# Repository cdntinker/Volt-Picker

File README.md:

This is a little USB-PD board that'll give you the selected output voltage if plugged into a PD capable source that supports the chosen voltage.

# Theory:
One of the main design criteria is that it does NOT require an MCU to manage it.

Voltage & Current are chosen by soldering a jumper for each.  (The basic circuit can easily be embeded into a board with just a single resistor for each...)

# Rant/Snark:
* Volt-Picker 1.tar.gz:
  * My original design idea
  * Based on the CH224 from Nanjing Qinheng Microelectronics Co., Ltd. (WCH)
  * chip seems to have been disontinued...
* Volt-Picker 2.tar.gz
  * New design based on the AP33771 from Diodes Incorporated
  * Apparently, this has been replaced by the AP33771C
  * But nobody has stock yet...
* This is now rev 3.0.0
  * Based on the AP33771C
  * Will it be the penultimate verion?
  * Only time will tell if there's a need for a rev 4...

# Notes:
FreeCAD's STEP export seems to have some sort of bug that occasionally causes random boolean cuts in CSG objects to act like boolean unions.  This is very weird and annoying.

My current solution (seems to work rather well...) is to go back into the project and add 0.001mm to a positional offset of the item that's being borked.

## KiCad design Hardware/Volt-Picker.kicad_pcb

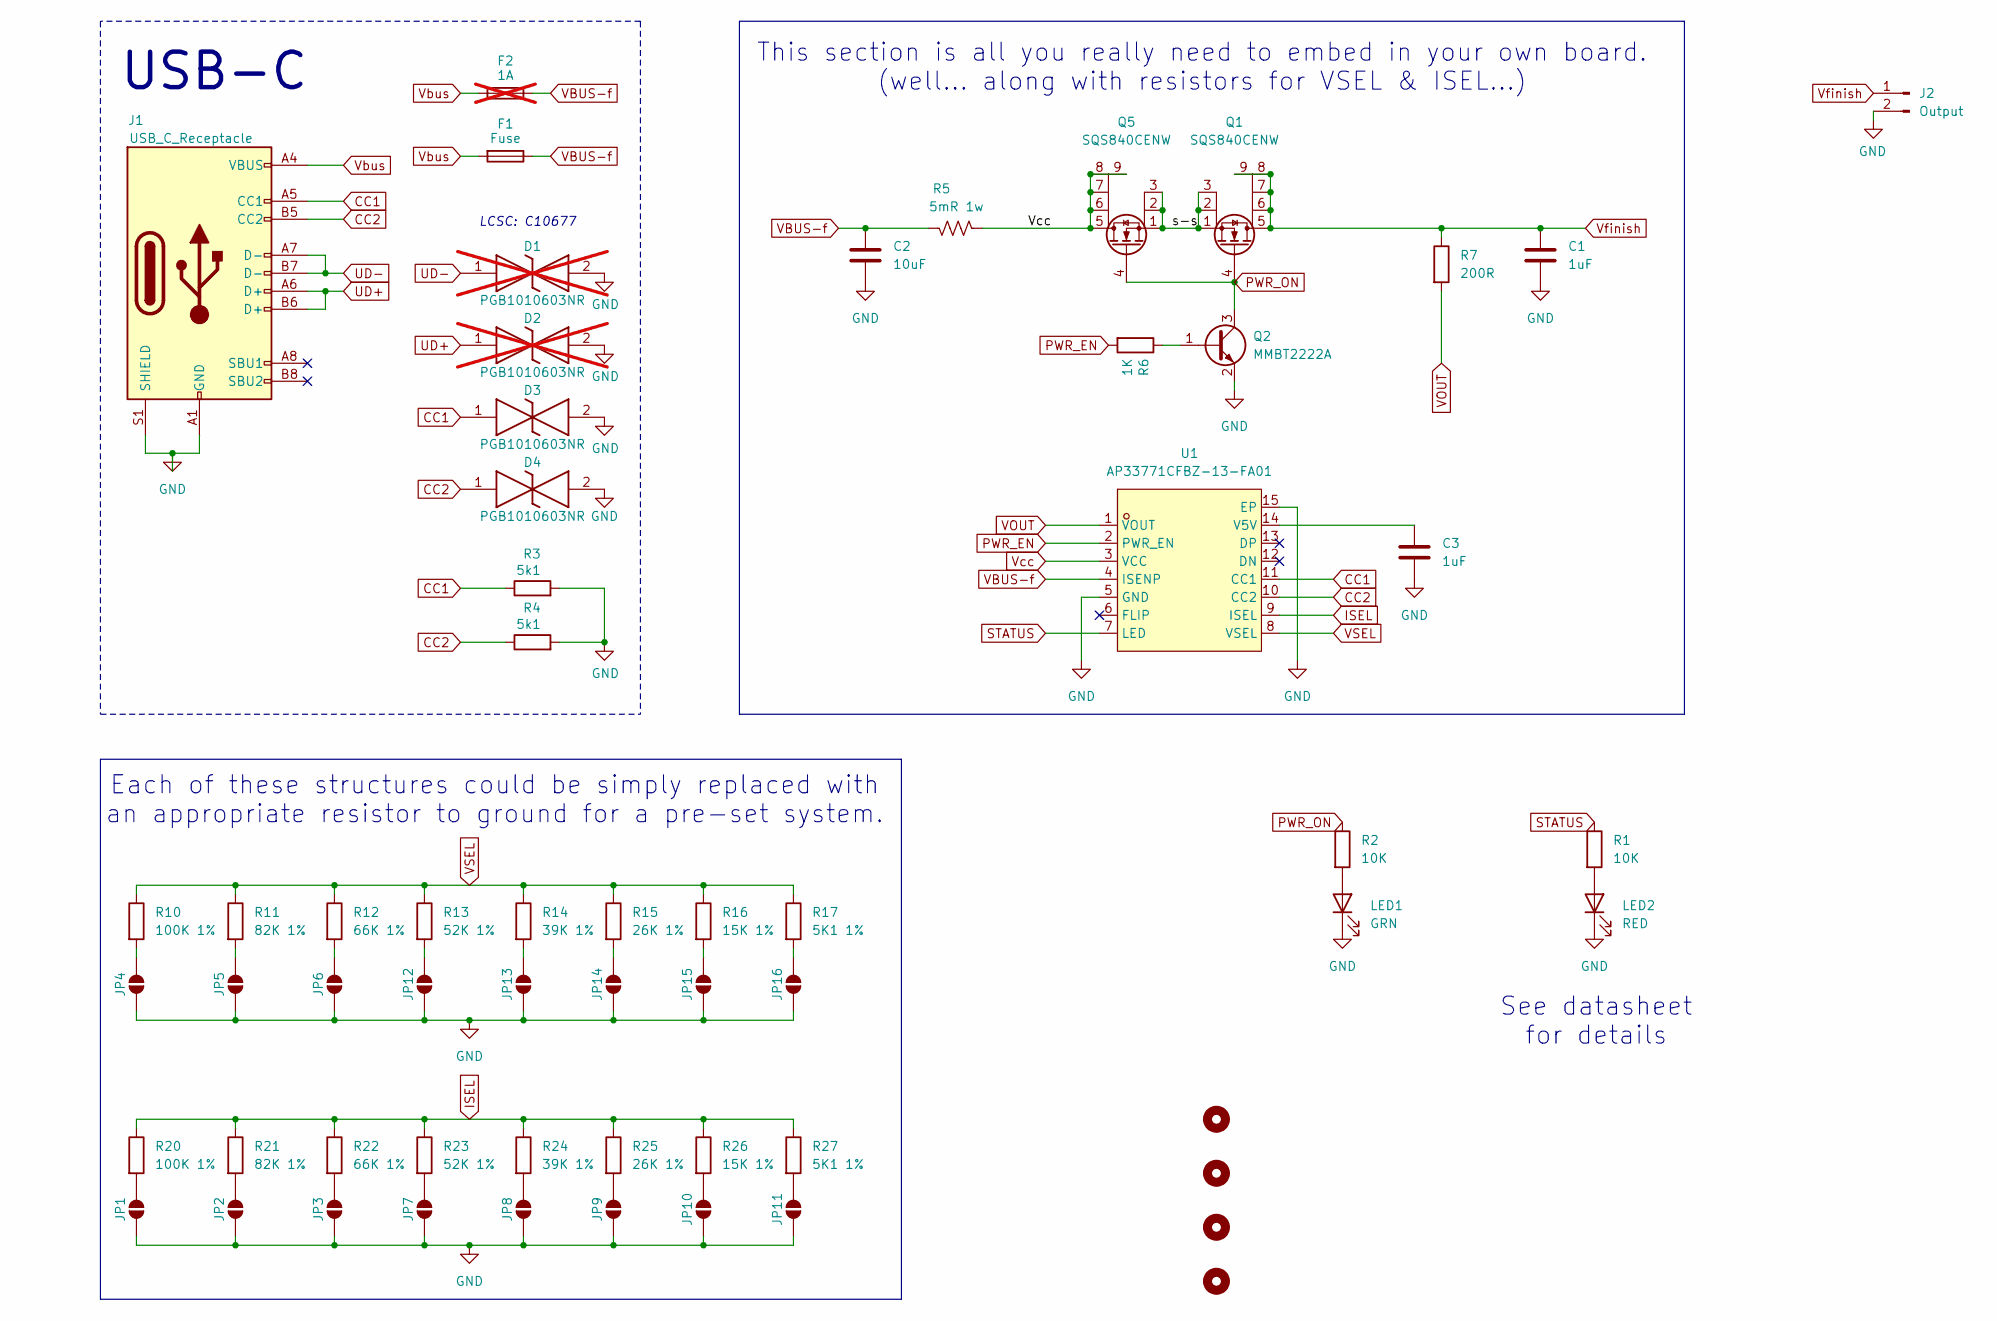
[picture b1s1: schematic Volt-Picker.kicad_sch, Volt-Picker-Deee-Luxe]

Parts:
C1: 1uF; C_0805_2012Metric; LCSC C28323
C2: 10uF; C_0805_2012Metric
C3: 1uF; C_0603_1608Metric; LCSC C28323
D1, D2: PGB1010603NR; PGB1010603NRHF; Manufacturer_Part_Number PGB1010603NR; Mouser Part Number 576-PGB1010603NR; not fitted
D3, D4: PGB1010603NR; PGB1010603NRHF; Manufacturer_Part_Number PGB1010603NR; Mouser Part Number 576-PGB1010603NR
F1: Fuse; Fuseholder_Littelfuse_Nano2_154x; LCSC Part C206922 (maybe)
F2: 1A; Fuse_1206_3216Metric_Pad1.42x1.75mm_HandSolder; LCSC C41367221; not fitted
H1, H2, H3, H4: MountingHole; MountingHole_3.2mm_M3_DIN965
J1: USB_C_Receptacle; USB_C_Receptacle_HRO_TYPE-C-31-M-12; LCSC C2765186
J2: Output; TerminalBlock_DG350-3.5-02P-14-00A(H); LCSC C2760668
JP1, JP2, JP3, JP4, JP5, JP6, JP7, JP8, JP9, JP10, JP11, JP12, JP13, JP14, JP15, JP16: SolderJumper_2_Open; tinySJ-Open (alt)
LED1: GRN; LED_0603_1608Metric; LCSC C2994781
LED2: RED; LED_0603_1608Metric; LCSC C2994781
Q1, Q5: SQS840CENW; POWERPAK-1212-8_L3.1-W3.1-P0.65-LS3.3-BL
Q2: MMBT2222A; SOT-23; LCSC Part C916372
R1, R2: 10K; R_0603_1608Metric
R3, R4: 5k1; R_0603_1608Metric; LCSC C23186
R5: 5mR 1w; R_1206_3216Metric
R6: 1K; R_0603_1608Metric; LCSC Part C22548
R7: 200R; R_0603_1608Metric
R10, R20: 100K 1%; R_0603_1608Metric
R11, R21: 82K 1%; R_0603_1608Metric
R12, R22: 66K 1%; R_0603_1608Metric
R13, R23: 52K 1%; R_0603_1608Metric
R14, R24: 39K 1%; R_0603_1608Metric
R15, R25: 26K 1%; R_0603_1608Metric
R16, R26: 15K 1%; R_0603_1608Metric
R17, R27: 5K1 1%; R_0603_1608Metric
U1: AP33771CFBZ-13-FA01; TDFN-14_L3.0-W3.0-P0.40-TL-EP; MPN AP33771CFBZ-13-FA01; LCSC Part C24735840

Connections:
/s-s: Q1.1 (S), Q1.2 (S), Q1.3 (S), Q5.1 (S), Q5.2 (S), Q5.3 (S)
CC1: D3.1, J1.A5 (CC1), R3.1, U1.11 (CC1)
CC2: D4.1, J1.B5 (CC2), R4.1, U1.10 (CC2)
GND: C1.2, C2.2, C3.2, D1.2, D2.2, D3.2, D4.2, J1.A1 (GND), J1.A12 (GND), J1.B1 (GND), J1.B12 (GND), J1.S1 (SHIELD), J2.2, JP1.1 (A), JP2.1 (A), JP3.1 (A), JP4.1 (A), JP5.1 (A), JP6.1 (A), JP7.1 (A), JP8.1 (A), JP9.1 (A), JP10.1 (A), JP11.1 (A), JP12.1 (A), JP13.1 (A), JP14.1 (A), JP15.1 (A), JP16.1 (A), LED1.1 (K), LED2.1 (K), Q2.2 (E), R3.2, R4.2, U1.5 (GND), U1.15 (EP)
ISEL: R20.1, R21.1, R22.1, R23.1, R24.1, R25.1, R26.1, R27.1, U1.9 (ISEL)
unnamed: JP1.2 (B), R20.2
unnamed: JP2.2 (B), R21.2
unnamed: JP3.2 (B), R22.2
unnamed: JP4.2 (B), R10.2
unnamed: JP5.2 (B), R11.2
unnamed: JP6.2 (B), R12.2
unnamed: JP7.2 (B), R23.2
unnamed: JP8.2 (B), R24.2
unnamed: JP9.2 (B), R25.2
unnamed: JP10.2 (B), R26.2
unnamed: JP11.2 (B), R27.2
unnamed: JP12.2 (B), R13.2
unnamed: JP13.2 (B), R14.2
unnamed: JP14.2 (B), R15.2
unnamed: JP15.2 (B), R16.2
unnamed: JP16.2 (B), R17.2
unnamed: LED1.2 (A), R2.2
unnamed: LED2.2 (A), R1.2
unnamed: Q2.1 (B), R6.1
unnamed: C3.1, U1.14 (V5V)
PWR_EN: R6.2, U1.2 (PWR_EN)
PWR_ON: Q1.4 (G), Q2.3 (C), Q5.4 (G), R2.1
STATUS: R1.1, U1.7 (LED)
UD+: D2.1, J1.A6 (D+), J1.B6 (D+)
UD-: D1.1, J1.A7 (D-), J1.B7 (D-)
VBUS-f: C2.1, F1.1, F2.2, R5.2, U1.4 (ISENP)
VOUT: R7.2, U1.1 (VOUT)
VSEL: R10.1, R11.1, R12.1, R13.1, R14.1, R15.1, R16.1, R17.1, U1.8 (VSEL)
Vbus: F1.2, F2.1, J1.A4 (VBUS), J1.A9 (VBUS), J1.B4 (VBUS), J1.B9 (VBUS)
Vcc: Q5.5 (D), Q5.6 (D), Q5.7 (D), Q5.8 (D), Q5.9 (D), R5.1, U1.3 (VCC)
Vfinish: C1.1, J2.1, Q1.5 (D), Q1.6 (D), Q1.7 (D), Q1.8 (D), Q1.9 (D), R7.1

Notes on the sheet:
USB-C
Each of these structures could be simply replaced with an appropriate resistor to ground for a pre-set system.
LCSC: C10677
See datasheet for details
This section is all you really need to embed in your own board. (well... along with resistors for VSEL & ISEL...)

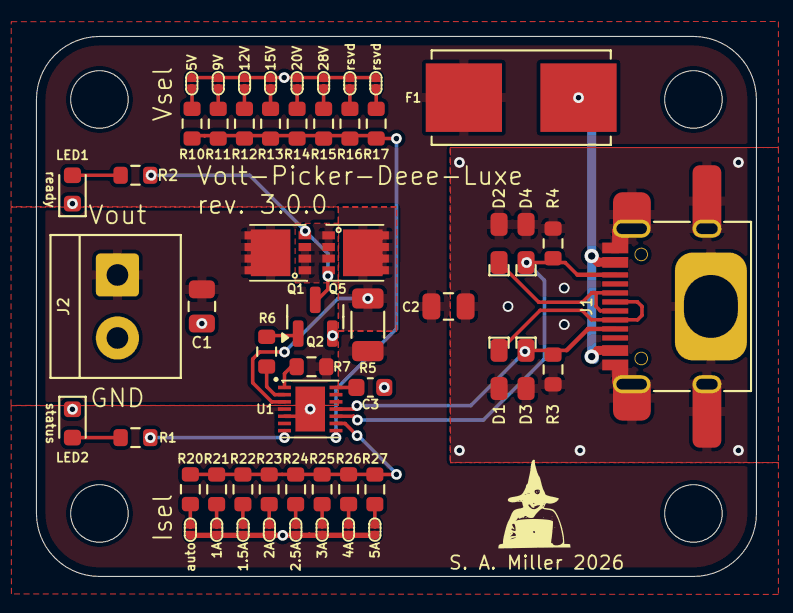
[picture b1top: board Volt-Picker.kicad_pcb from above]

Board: 2 copper layers, 40.0 x 30.0 mm, 59 parts (0 on the bottom side), 36 nets.

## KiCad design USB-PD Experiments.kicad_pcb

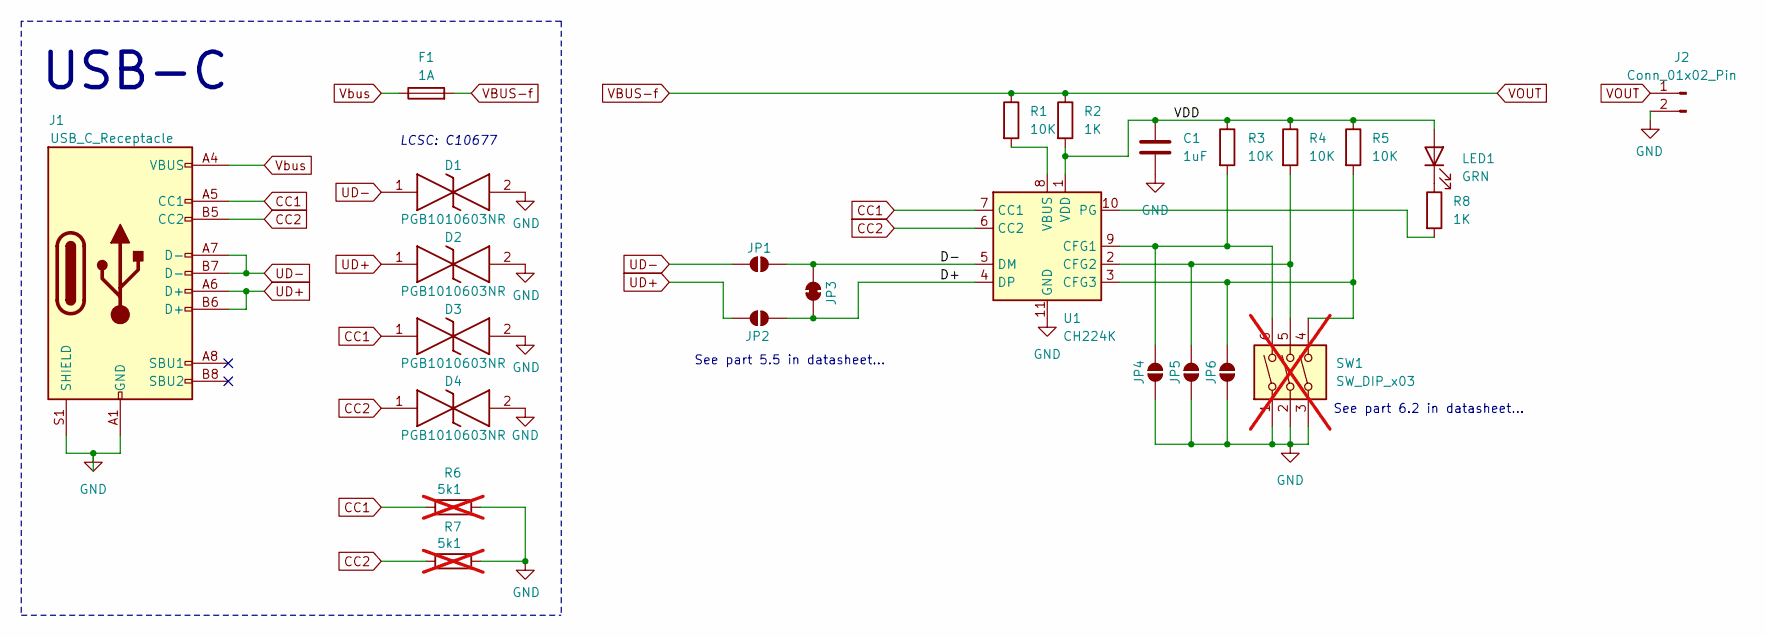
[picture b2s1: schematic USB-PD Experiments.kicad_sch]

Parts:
C1: 1uF; C_0805_2012Metric; LCSC C28323
D1, D2, D3, D4: PGB1010603NR; PGB1010603NRHF; Manufacturer_Part_Number PGB1010603NR; Mouser Part Number 576-PGB1010603NR
F1: 1A; Fuse_1206_3216Metric_Pad1.42x1.75mm_HandSolder; LCSC C41367221
J1: USB_C_Receptacle; USB_C_Receptacle_HRO_TYPE-C-31-M-12; LCSC C2765186
J2: Conn_01x02_Pin; TerminalBlock_DG350-3.5-02P-14-00A(H); LCSC C2760668
JP1, JP2: SolderJumper_2_Open; tinySJ-Open
JP3: SolderJumper_2_Bridged; smallSJ-Bridged
JP4, JP5, JP6: SolderJumper_2_Open; tinySJ-Open (alt)
LED1: GRN; LED_0603_1608Metric; LCSC C2994781
R1, R3, R4, R5: 10K; R_0603_1608Metric; LCSC C25804
R2, R8: 1K; R_0603_1608Metric; LCSC C21190
R6, R7: 5k1; R_0603_1608Metric; LCSC C23186; not fitted
SW1: SW_DIP_x03; SW_DIP_SPSTx03_Slide_KingTek_DSHP03TJ_W5.25mm_P1.27mm_JPin; LCSC C19272175; not fitted
U1: CH224K; SSOP-10-1EP_3.9x4.9mm_P1mm_EP2.1x3.3mm; LCSC C970725

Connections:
/D+: JP2.2 (B), JP3.1 (A), U1.4 (DP)
/D-: JP1.2 (B), JP3.2 (B), U1.5 (DM)
/VDD: C1.1, LED1.2 (A), R2.2, R3.1, R4.1, R5.1, U1.1 (VDD)
CC1: D3.1, J1.A5 (CC1), R6.1, U1.7 (CC1)
CC2: D4.1, J1.B5 (CC2), R7.1, U1.6 (CC2)
GND: C1.2, D1.2, D2.2, D3.2, D4.2, J1.A1 (GND), J1.A12 (GND), J1.B1 (GND), J1.B12 (GND), J1.S1 (SHIELD), J2.2, JP4.1 (A), JP5.1 (A), JP6.1 (A), R6.2, R7.2, SW1.1, SW1.2, SW1.3, U1.11 (GND)
unnamed: JP4.2 (B), R3.2, SW1.6, U1.9 (CFG1)
unnamed: JP5.2 (B), R4.2, SW1.5, U1.2 (CFG2)
unnamed: JP6.2 (B), R5.2, SW1.4, U1.3 (CFG3)
unnamed: LED1.1 (K), R8.1
unnamed: R8.2, U1.10 (PG)
unnamed: R1.2, U1.8 (VBUS)
UD+: D2.1, J1.A6 (D+), J1.B6 (D+), JP2.1 (A)
UD-: D1.1, J1.A7 (D-), J1.B7 (D-), JP1.1 (A)
VBUS-f: F1.2, J2.1, R1.1, R2.1
Vbus: F1.1, J1.A4 (VBUS), J1.A9 (VBUS), J1.B4 (VBUS), J1.B9 (VBUS)

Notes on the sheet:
See part 5.5 in datasheet...
USB-C
See part 6.2 in datasheet...
LCSC: C10677

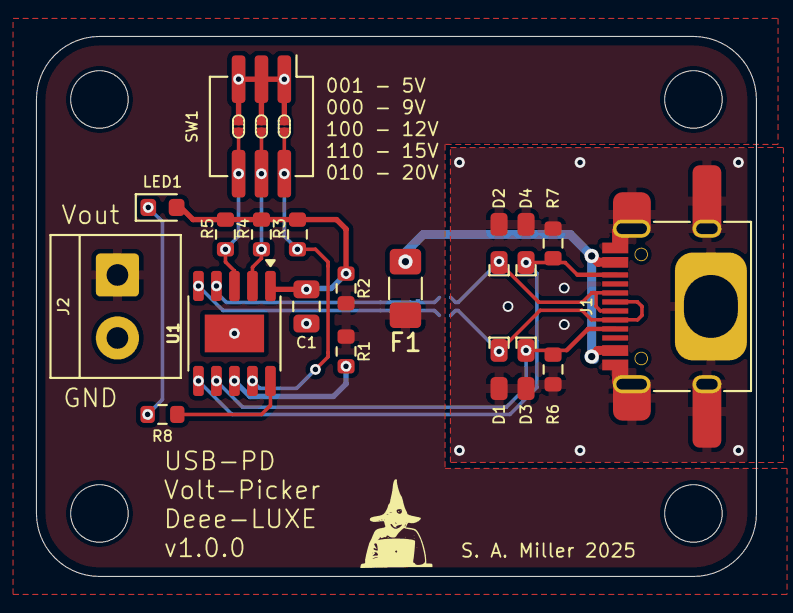
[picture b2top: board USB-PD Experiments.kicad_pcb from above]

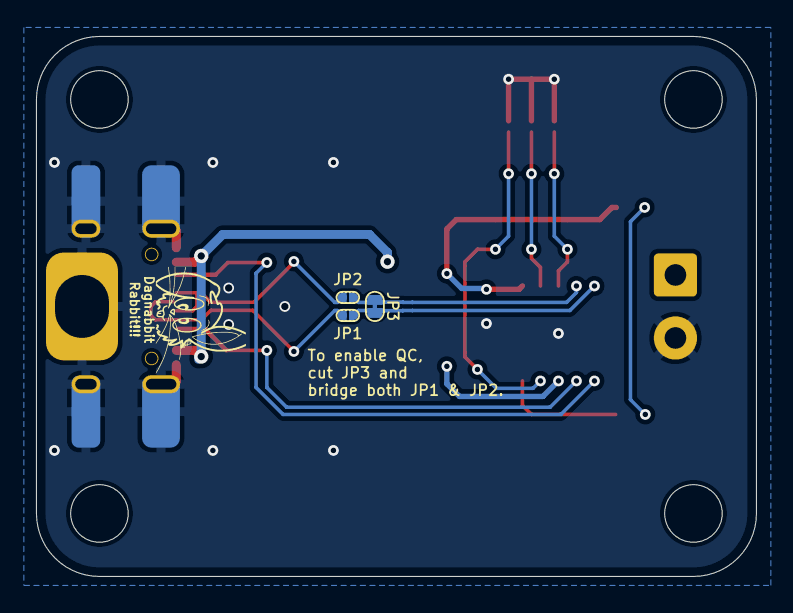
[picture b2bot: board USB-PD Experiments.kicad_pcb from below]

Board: 2 copper layers, 40.0 x 30.0 mm, 25 parts (3 on the bottom side), 16 nets.
